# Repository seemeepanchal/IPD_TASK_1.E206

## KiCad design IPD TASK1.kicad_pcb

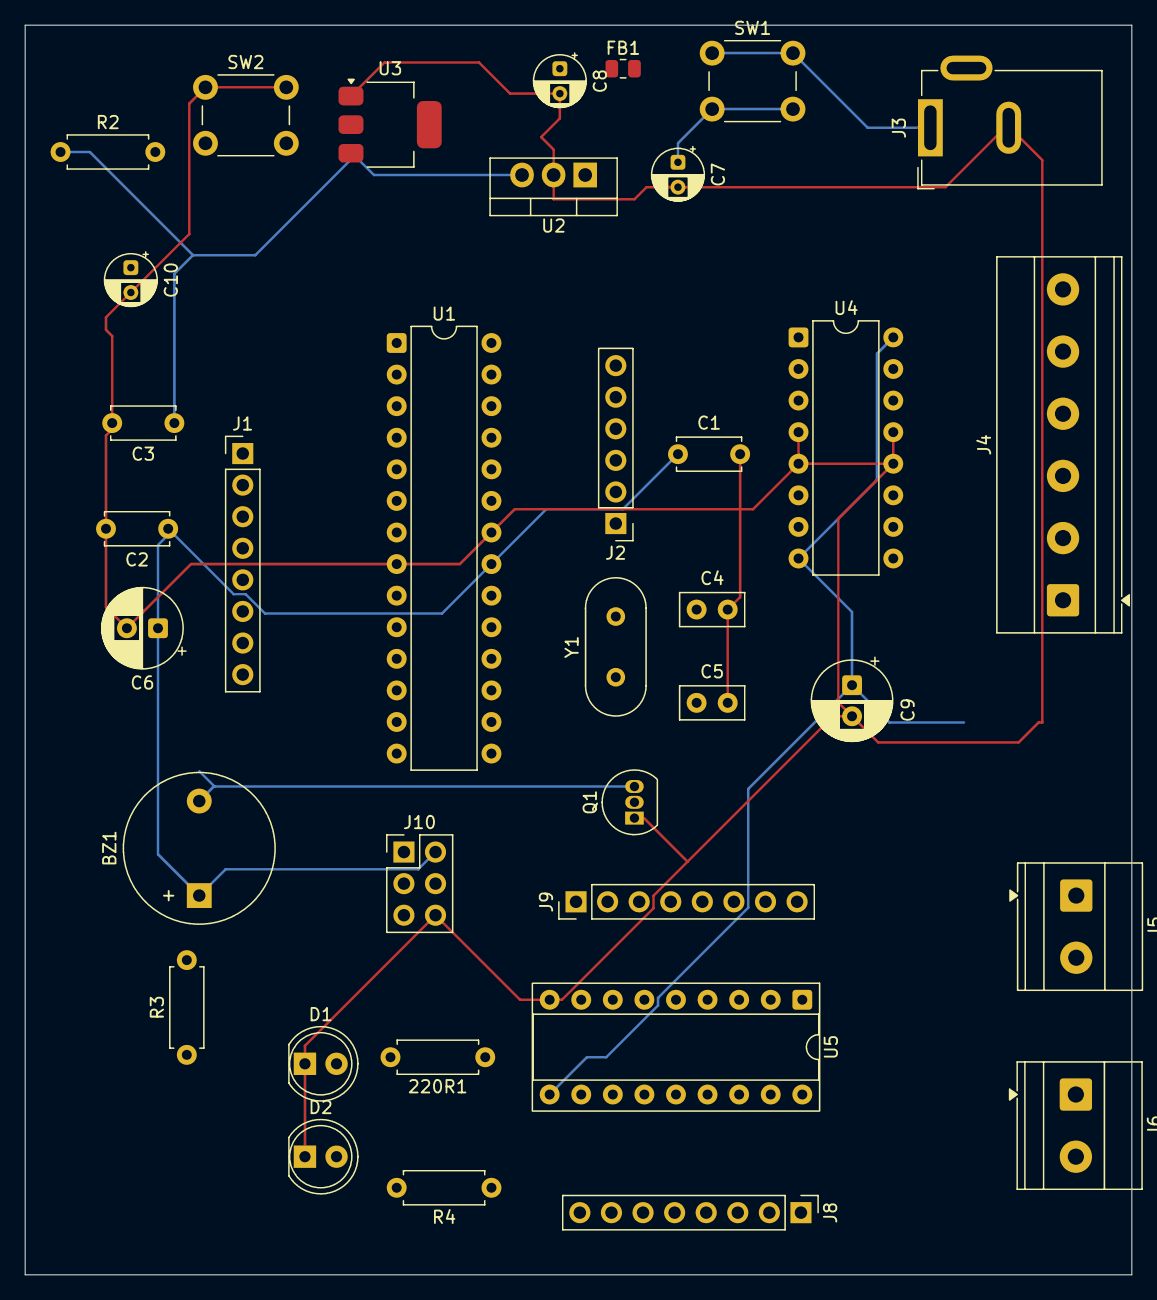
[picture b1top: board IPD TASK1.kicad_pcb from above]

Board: 8 copper layers, 89.0 x 100.5 mm, 36 parts (0 on the bottom side), 59 nets.

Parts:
220R1: R; R_Axial_DIN0207_L6.3mm_D2.5mm_P7.62mm_Horizontal
BZ1: Buzzer; Buzzer_12x9.5RM7.6
C1, C2, C3: 100nf; C_Disc_D5.0mm_W2.5mm_P5.00mm
C4, C5: 22pf; C_Disc_D5.0mm_W2.5mm_P2.50mm
C6: 10uf; CP_Radial_D6.3mm_P2.50mm
C7, C8: 1uf; CP_Radial_D4.0mm_P2.00mm
C9: 100uf; CP_Radial_D6.3mm_P2.50mm
C10: 1UF; CP_Radial_D4.0mm_P2.00mm
D1, D2: LED; LED_D5.0mm
FB1: FerriteBead; R_0805_2012Metric
J1, J8, J9: Conn_01x08; PinHeader_1x08_P2.54mm_Vertical
J2: Conn_01x06; PinHeader_1x06_P2.54mm_Vertical
J3: Barrel_Jack; BarrelJack_GCT_DCJ200-10-A_Horizontal
J4: Screw_Terminal_01x06; TerminalBlock_Phoenix_MKDS-1,5-6_1x06_P5.00mm_Horizontal
J5, J6: Screw_Terminal_01x02; TerminalBlock_Phoenix_MKDS-1,5-2_1x02_P5.00mm_Horizontal
J10: Conn_02x03_Odd_Even; PinHeader_2x03_P2.54mm_Vertical
Q1: 2N7000; TO-92_Inline
R2: 1K; R_Axial_DIN0207_L6.3mm_D2.5mm_P7.62mm_Horizontal
R3: 10K; R_Axial_DIN0207_L6.3mm_D2.5mm_P7.62mm_Horizontal
R4: 220R; R_Axial_DIN0207_L6.3mm_D2.5mm_P7.62mm_Horizontal
SW1, SW2: SW_Push; SW_PUSH_6mm
U1: ATmega328-P; DIP-28_W7.62mm
U2: L7805; TO-220-3_Vertical
U3: AMS1117; SOT-223-3_TabPin2
U4: L293; DIP-16_W7.62mm
U5: ULN2803A; DIP-18_W7.62mm_Socket
Y1: Crystal; Crystal_HC49-U_Vertical

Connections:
5V: BZ1.1 (+), C1.1, C2.1, C3.1, C6.1, J10.2, R2.1, U1.7 (VCC), U1.20 (AVCC), U1.21 (AREF), U2.3 (OUT), U3.3 (VI)
12V: C9.1, J3.1, U4.8 (VCC2), U4.16 (VCC1), U5.10 (COM)
GND: C1.2, C2.2, C3.2, C4.2, C5.2, C6.2, C9.2, C10.2, D1.1 (K), D2.1 (K), J3.2, J10.6, Q1.1 (S), SW2.1, U1.8 (GND), U1.22 (GND), U4.4 (GND), U4.5 (GND), U4.12 (GND), U4.13 (GND), U5.9 (GND)
GPIO_FLAG_1: 220R1.1, U1.14 (PB0)
GPIO_FLAG_2: R4.1, U1.15 (PB1)
MISO: J10.1, U1.18 (PB4)
MOSI: J10.4, U1.17 (PB3)
unnamed: BZ1.2 (-), Q1.3 (D)
unnamed: C7.1, FB1.2, SW1.2
unnamed: 220R1.2, D1.2 (A)
unnamed: D2.2 (A), R4.2
unnamed: J1.1, U1.2 (PD0)
unnamed: J1.2, U1.3 (PD1)
unnamed: J1.3, U1.4 (PD2)
unnamed: J1.4, U1.5 (PD3)
unnamed: J1.5, U1.6 (PD4)
unnamed: J1.6, U1.11 (PD5)
unnamed: J1.7, U1.12 (PD6)
unnamed: J1.8, U1.13 (PD7)
unnamed: J2.1, U1.23 (PC0)
unnamed: J2.2, U1.24 (PC1)
unnamed: J2.3, U1.25 (PC2)
unnamed: J2.4, U1.26 (PC3)
unnamed: J2.5, U1.27 (PC4)
unnamed: J2.6, U1.28 (PC5)
unnamed: J4.1, U4.9 (EN3,4)
unnamed: J4.2, U4.15 (4A)
unnamed: J4.3, U4.10 (3A)
unnamed: J4.4, U4.1 (EN1,2)
unnamed: J4.5, U4.7 (2A)
unnamed: J4.6, U4.2 (1A)
unnamed: J5.1, U4.3 (1Y)
unnamed: J5.2, U4.6 (2Y)
unnamed: J6.1, U4.11 (3Y)
unnamed: J6.2, U4.14 (4Y)
unnamed: J8.1, U5.18 (O1)
unnamed: J8.2, U5.17 (O2)
unnamed: J8.3, U5.16 (O3)
unnamed: J8.4, U5.15 (O4)
unnamed: J8.5, U5.14 (O5)
unnamed: J8.6, U5.13 (O6)
unnamed: J8.7, U5.12 (O7)
unnamed: J8.8, U5.11 (O8)
unnamed: J9.1, U5.8 (I8)
unnamed: J9.2, U5.7 (I7)
unnamed: J9.3, U5.6 (I6)
unnamed: J9.4, U5.5 (I5)
unnamed: J9.5, U5.4 (I4)
unnamed: J9.6, U5.3 (I3)
unnamed: J9.7, U5.2 (I2)
unnamed: J9.8, U5.1 (I1)
unnamed: Q1.2 (G), R3.1
unnamed: C4.1, U1.9 (XTAL1/PB6), Y1.2
unnamed: C5.1, U1.10 (XTAL2/PB7), Y1.1
unnamed: C7.2, C8.2, U2.2 (GND), U3.1 (ADJ)
unnamed: C8.1, FB1.1, U2.1 (IN)
PWM1: R3.2, U1.16 (PB2)
Reset: C10.1, J10.5, R2.2, SW2.2, U1.1 (~RESET/PC6)
SCK: J10.3, U1.19 (PB5)

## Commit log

2026-03-01 Updated Image
2026-03-01 Minor Fixes
